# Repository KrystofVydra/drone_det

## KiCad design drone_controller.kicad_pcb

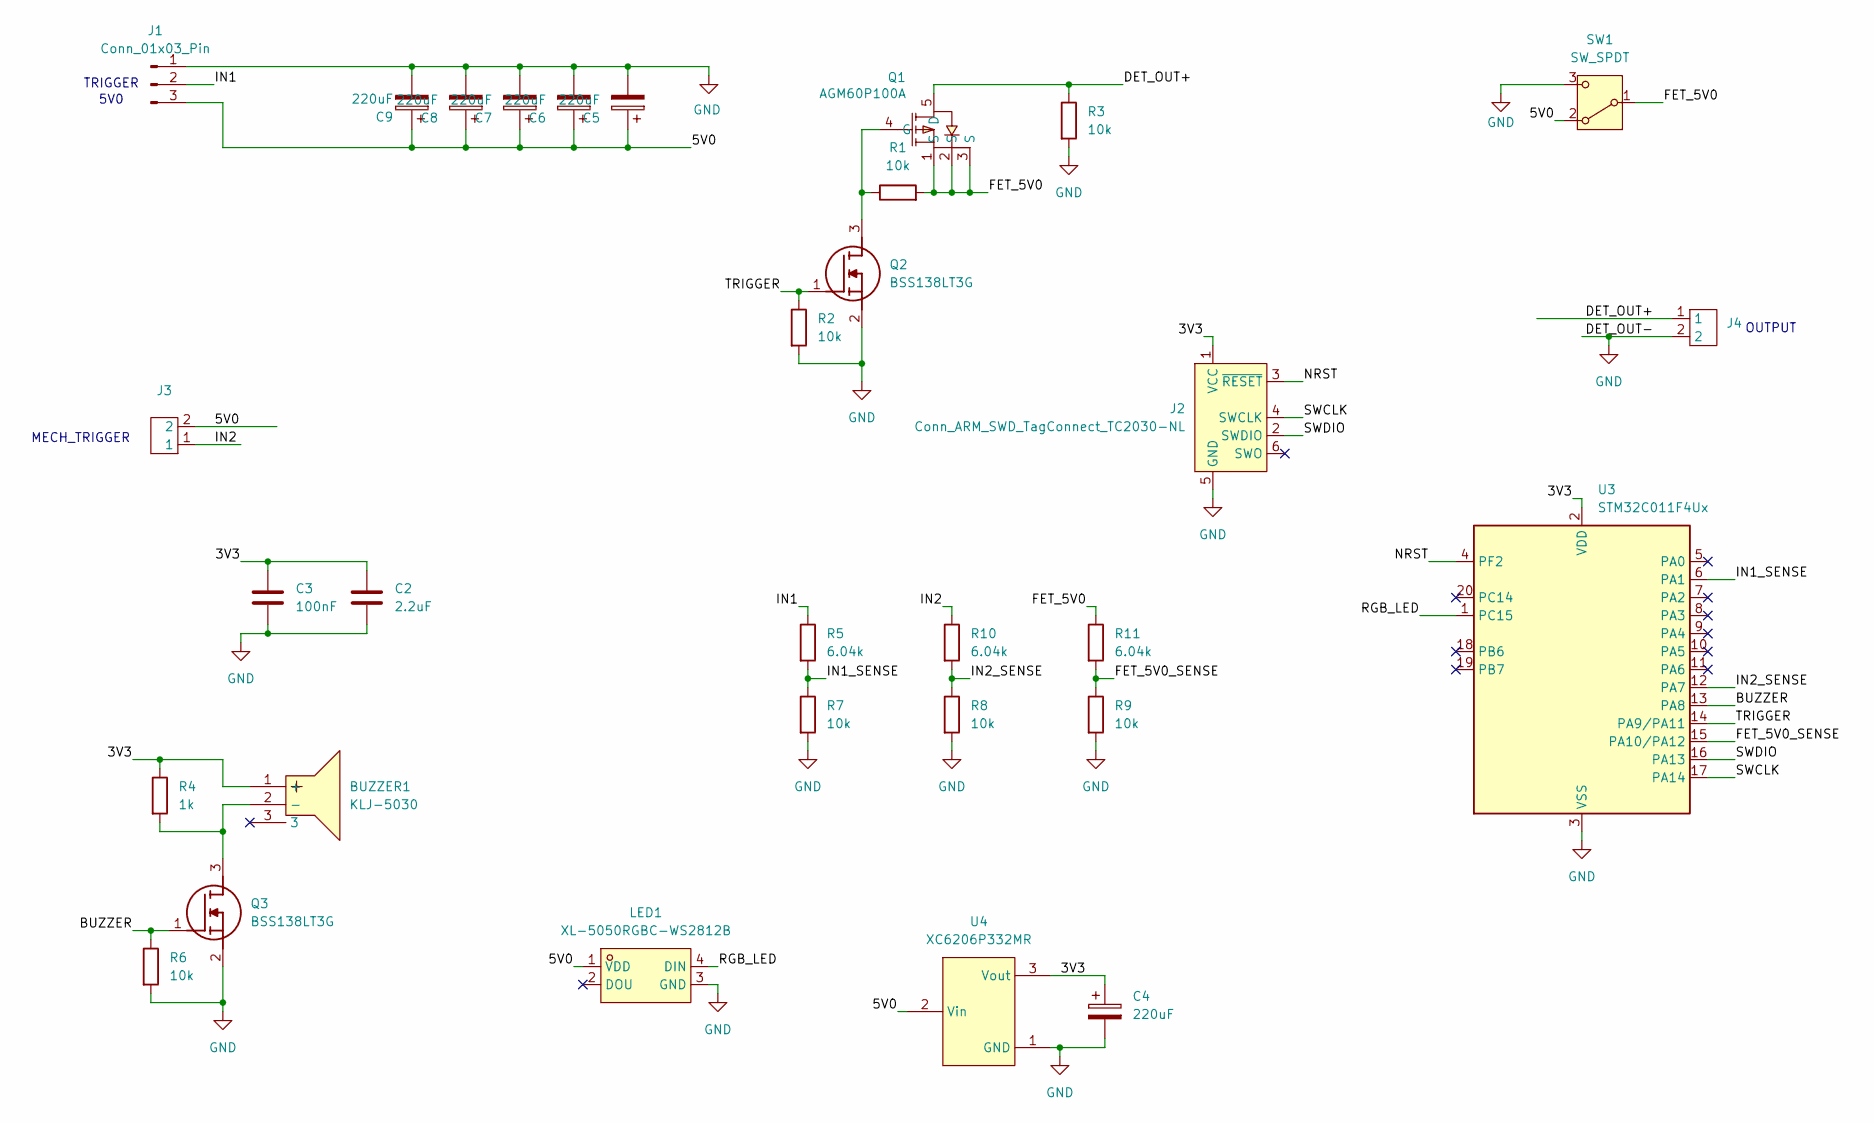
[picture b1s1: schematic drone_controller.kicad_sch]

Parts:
BUZZER1: KLJ-5030; BUZ-SMD_4P-L5.0-W5.0-P3.80-TL; LCSC Part C201044
C2: 2.2uF; C_0603_1608Metric; LCSC Part C23630
C3: 100nF; C_0402_1005Metric; LCSC Part C60474
C4, C5, C6, C7, C8, C9: 220uF; CAP-SMD_L3.5-W2.8-FD; LCSC Part C2887903
J1: Conn_01x03_Pin; PinHeader_1x03_P2.54mm_Vertical
J2: Conn_ARM_SWD_TagConnect_TC2030-NL; Tag-Connect_TC2030-IDC-NL_2x03_P1.27mm_Vertical
J3, J4: CONN-TH_XY118-5.0-2P; LCSC Part C784922
LED1: XL-5050RGBC-WS2812B; LED-SMD_4P-L5.0-W5.0-BL_XL-5050RGBC; LCSC Part C2843785
Q1: AGM60P100A; TDSON-8_L5.9-W5.2-P1.27-BL; LCSC Part C5373096
Q2, Q3: BSS138LT3G; SOT96P237X111-3N; LCSC Part BSS138LT3G
R1, R2, R3, R6, R7, R8, R9: 10k; R_0201_0603Metric; LCSC Part C106225
R4: 1k; R_0201_0603Metric; LCSC Part C138165
R5, R10, R11: 6.04k; R_0201_0603Metric; LCSC Part C364363
SW1: SW_SPDT; D2HW-BL201DL; LCSC Part D2HW-BL201DL
U3: STM32C011F4Ux; ST_UFQFPN-20_3x3mm_P0.5mm; LCSC Part C5456188
U4: XC6206P332MR; SOT-23-3_L2.9-W1.6-P1.90-LS2.8-BR; LCSC Part C5446

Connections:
/3V3: BUZZER1.1 (+), C2.1, C3.1, C4.1, J2.1 (VCC), R4.1, U3.2 (VDD), U4.3 (Vout)
/5V0: C5.1, C6.1, C7.1, C8.1, C9.1, J1.3, J3.2, LED1.1 (VDD), SW1.2 (A), U4.2 (Vin)
/BUZZER: Q3.1 (G), R6.1, U3.13 (PA8)
/DET_OUT+: J4.1, Q1.5 (D), R3.1
/FET_5V0: Q1.1 (S), Q1.2 (S), Q1.3 (S), R1.2, R11.1, SW1.1 (B)
/FET_5V0_SENSE: R9.1, R11.2, U3.15 (PA10/PA12)
/IN1: J1.2, R5.1
/IN1_SENSE: R5.2, R7.1, U3.6 (PA1)
/IN2: J3.1, R10.1
/IN2_SENSE: R8.1, R10.2, U3.12 (PA7)
/NRST: J2.3 (~RESET), U3.4 (PF2)
/RGB_LED: LED1.4 (DIN), U3.1 (PC15)
/SWCLK: J2.4 (SWCLK), U3.17 (PA14)
/SWDIO: J2.2 (SWDIO), U3.16 (PA13)
/TRIGGER: Q2.1 (G), R2.1, U3.14 (PA9/PA11)
GND: C2.2, C3.2, C4.2, C5.2, C6.2, C7.2, C8.2, C9.2, J1.1, J2.5 (GND), J4.2, LED1.3 (GND), Q2.2 (S), Q3.2 (S), R2.2, R3.2, R6.2, R7.2, R8.2, R9.2, SW1.3 (C), U3.3 (VSS), U4.1 (GND)
unnamed: BUZZER1.2 (-), Q3.3 (D), R4.2
unnamed: Q1.4 (G), Q2.3 (D), R1.1

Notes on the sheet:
5V0
OUTPUT
MECH_TRIGGER
TRIGGER

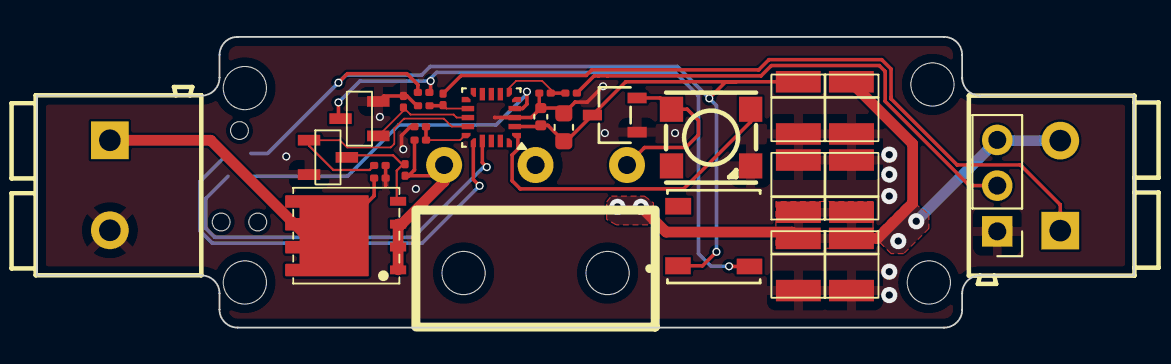
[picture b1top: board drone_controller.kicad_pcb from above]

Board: 2 copper layers, 60.9 x 16.1 mm, 31 parts (1 on the bottom side), 18 nets.

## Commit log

2025-07-01 second release v1.0 production freeze
2025-07-09 v2.0 release production freeze
